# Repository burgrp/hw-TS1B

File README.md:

# hw-TS1B
RF ISM Temperature sensor

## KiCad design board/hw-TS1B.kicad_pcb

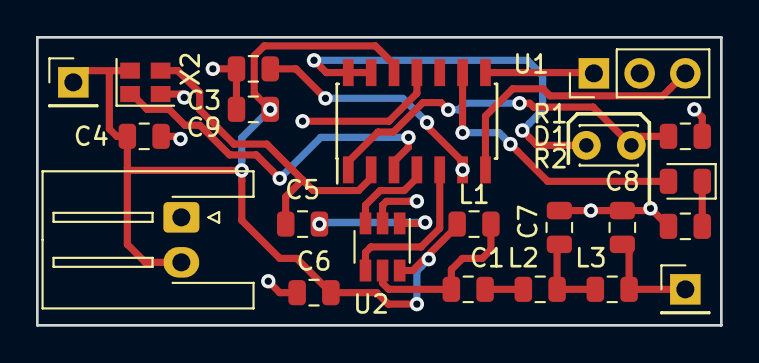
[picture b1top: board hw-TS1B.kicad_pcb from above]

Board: 2 copper layers, 38.0 x 16.0 mm, 22 parts (0 on the bottom side), 18 nets.

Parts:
AE1: Antenna; PinHeader_1x01_P2.54mm_Vertical
C1: 68pF; C_0805_2012Metric
C3, C4, C5, C6, C9: 100n; C_0805_2012Metric
C7, C8: 15pF; C_0805_2012Metric
D1: LED RED; LED_0805_2012Metric
J1: 3V3; PinHeader_1x01_P2.54mm_Vertical
J2: Conn_01x02; JST_XH_S2B-XH-A-1_1x02_P2.50mm_Horizontal
L1: 180nH; L_0805_2012Metric
L2: 36nH; L_0805_2012Metric
L3: 18nH; L_0805_2012Metric
R1: 10k 1%; R_0805_2012Metric
R2: 270R; R_0805_2012Metric
TH1: NTC 10k 3950 1%; C_Disc_D3.0mm_W2.0mm_P2.50mm
U1: ATSAMD11C14A-SS; SOIC-14_3.9x8.7mm_P1.27mm
U2: CMT2110A; TSOT-23-6
X1: SWD; PinHeader_1x03_P2.54mm_Vertical
X2: SG-210STF; Oscillator_SMD_SeikoEpson_SG210-4Pin_2.5x2.0mm

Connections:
/26MHZ: C5.2, U1.2, X2.3
/LED: D1.2, U1.9
/OSC_EN: U1.3, X2.1
/RF_CLK: U1.5, U2.4
/RF_DATA: U1.4, U2.3
/SWCLK: U1.7, X1.3
/SWDIO: U1.8, X1.1
/TEMP_PWR: TH1.1, U1.13, U1.14
/TEMP_SNS: R1.1, TH1.2, U1.1
GND: C3.2, C4.2, C6.2, C7.1, C8.1, C9.2, J2.1, R1.2, R2.1, U1.11, U2.2, X1.2, X2.2
unnamed: AE1.1, C8.2, L3.2
unnamed: C1.1, L2.1
unnamed: C1.2, L1.2, U2.5
unnamed: C3.1, U1.6
unnamed: C5.1, U2.1
unnamed: C7.2, L2.2, L3.1
unnamed: D1.1, R2.2
VDD: C4.1, C6.1, C9.1, J1.1, J2.2, L1.1, U1.12, U2.6, X2.4
